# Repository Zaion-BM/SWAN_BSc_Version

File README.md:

# SWAN BSc Thesis
Smart Watering Automation Network (SWAN) is a university thesis project at BME-VIK-MIT

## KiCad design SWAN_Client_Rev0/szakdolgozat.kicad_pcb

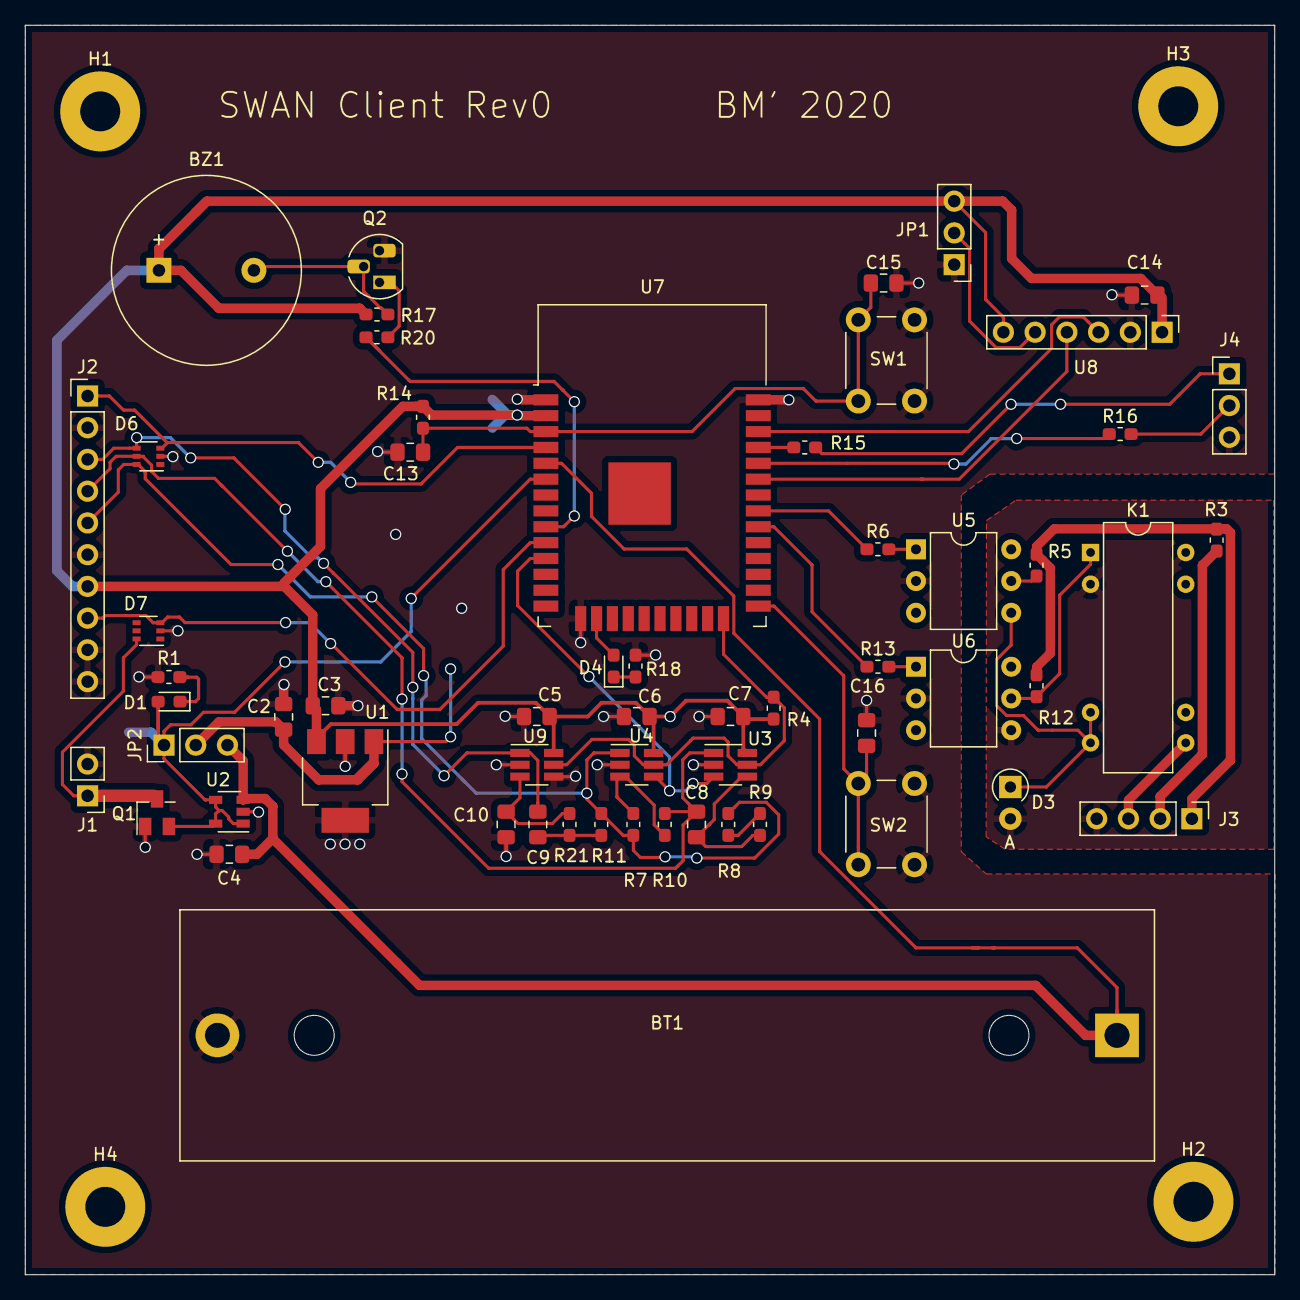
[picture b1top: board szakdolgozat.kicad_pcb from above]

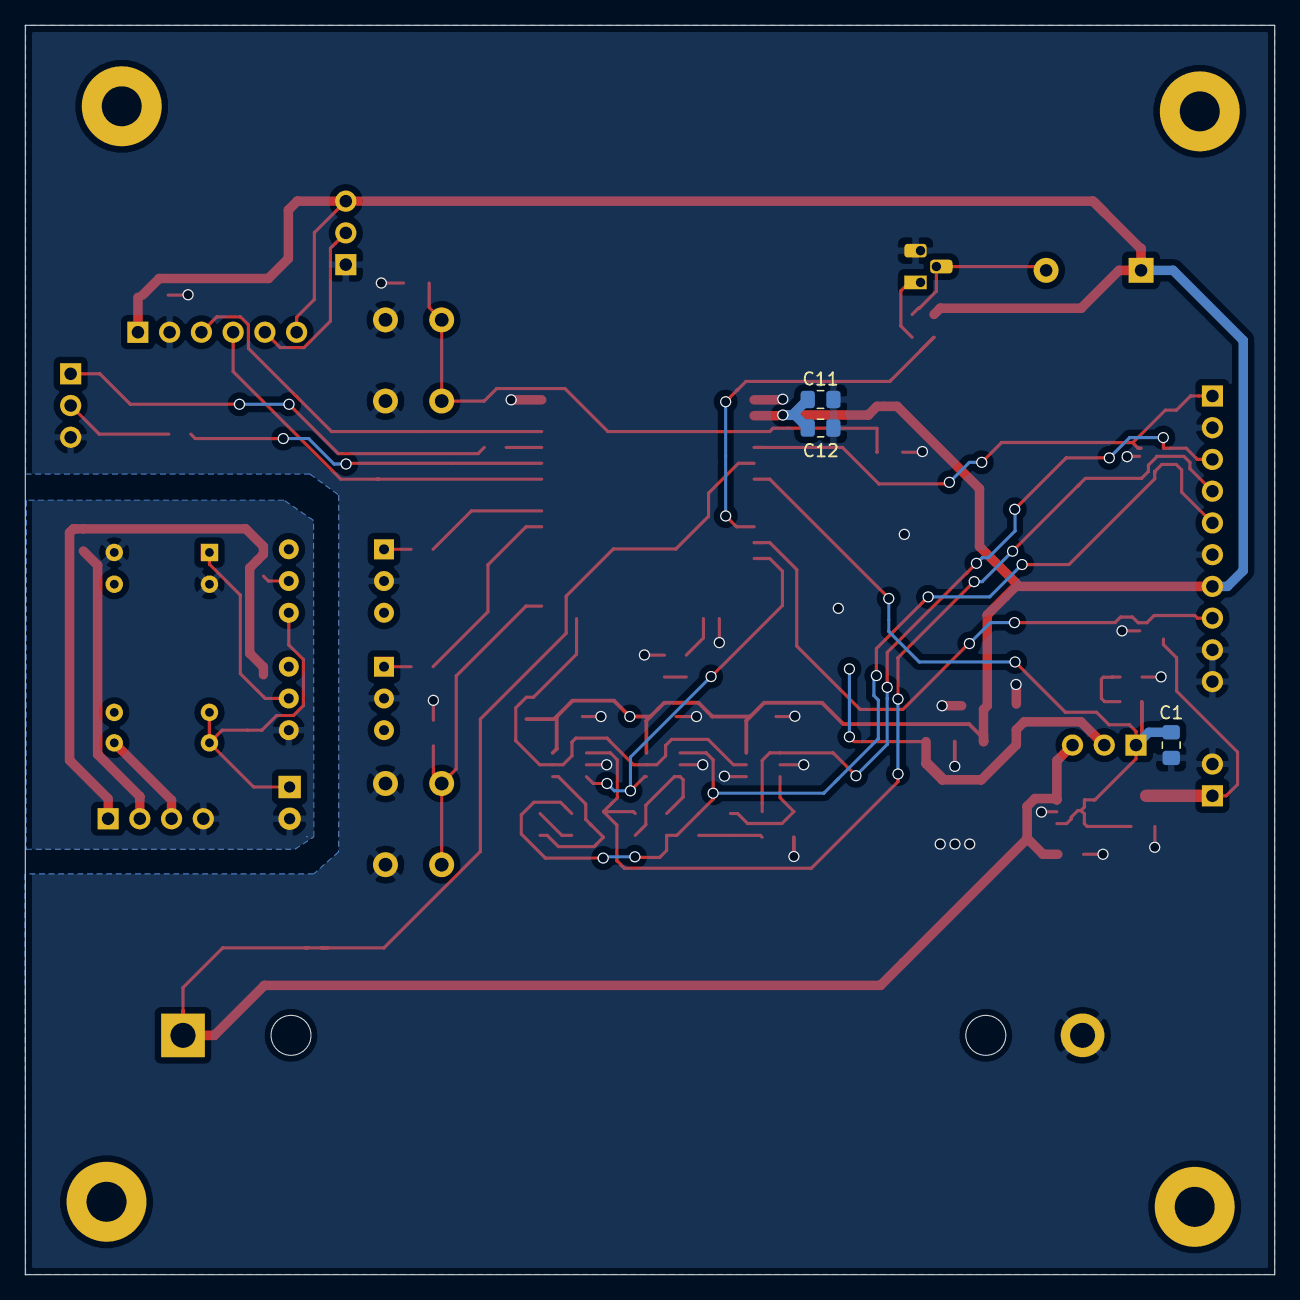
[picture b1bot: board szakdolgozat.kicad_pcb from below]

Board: 2 copper layers, 100.0 x 100.0 mm, 66 parts (3 on the bottom side), 44 nets.

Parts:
BT1: Battery_Cell; BatteryHolder_MPD_BH-18650-PC2
BZ1: Buzzer; Buzzer_15x7.5RM7.6
C1, C2, C3, C4: 1u; C_0805_2012Metric_Pad1.15x1.40mm_HandSolder
C5, C6, C7, C14: 100n; C_0805_2012Metric_Pad1.15x1.40mm_HandSolder
C8: 100p; C_0805_2012Metric_Pad1.15x1.40mm_HandSolder
C9, C10: 10p; C_0805_2012Metric_Pad1.15x1.40mm_HandSolder
C11, C13, C15, C16: 0.1u; C_0805_2012Metric_Pad1.15x1.40mm_HandSolder
C12: 22u; C_0805_2012Metric_Pad1.15x1.40mm_HandSolder
D1, D4: LED; LED_0603_1608Metric_Pad1.05x0.95mm_HandSolder
D3: D; D_A-405_P2.54mm_Vertical_AnodeUp
D6, D7: SP0505BAJT; SOT-363_SC-70-6
H1, H2, H3, H4: MountingHole; MountingHole_3.2mm_M3_Pad
J1: Barrel_Jack; PinHeader_1x02_P2.54mm_Vertical
J2: Conn_01x10_Female; PinHeader_1x10_P2.54mm_Vertical
J3: Conn_01x04_Female; PinHeader_1x04_P2.54mm_Vertical
J4: Conn_01x03_Female; PinHeader_1x03_P2.54mm_Vertical
JP1, JP2: Jumper_NC_Dual; PinHeader_1x03_P2.54mm_Vertical
K1: DIPxx-2Axx-21x; Relay_StandexMeder_DIP_LowProfile
Q1: Q_PMOS_DGS; MySuperSOT-3
Q2: Q_NPN_BCE; TO-92_HandSolder
R1, R14, R17, R18, R20: R; R_0603_1608Metric_Pad1.05x0.95mm_HandSolder
R3: 24R; R_0603_1608Metric_Pad1.05x0.95mm_HandSolder
R4: 100k; R_0603_1608Metric_Pad1.05x0.95mm_HandSolder
R5, R12: 12k; R_0603_1608Metric_Pad1.05x0.95mm_HandSolder
R6, R13: 160R; R_0603_1608Metric_Pad1.05x0.95mm_HandSolder
R7: 68k; R_0603_1608Metric_Pad1.05x0.95mm_HandSolder
R8: 1k; R_0603_1608Metric_Pad1.05x0.95mm_HandSolder
R9: 47; R_0603_1608Metric_Pad1.05x0.95mm_HandSolder
R10, R11, R21: 10k; R_0603_1608Metric_Pad1.05x0.95mm_HandSolder
R15, R16: 22R; R_0603_1608Metric_Pad1.05x0.95mm_HandSolder
SW1, SW2: SW_Push; SW_PUSH_6mm
U1: MCP1826S; SOT-223-3_TabPin2
U2: MCP73811T-420I-OT; SOT-23-5
U3, U4, U9: MCP6273-E_CH; SOT-23-6_Handsoldering
U5, U6: CNY17-1; DIP-6_W7.62mm
U7: ESP32-WROOM-32
U8: BMP280_PCB; PinHeader_1x06_P2.54mm_Vertical

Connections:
+3V3: BZ1.1, C3.1, C5.1, C6.1, C7.1, C11.1, C12.1, C14.1, J2.7, JP1.3, R4.1, R14.1, R17.1, U1.3, U3.6, U4.6, U7.2, U8.1, U8.6, U9.6
+12V: J3.1, R3.1, R5.1, R12.1
/1V65_REF: U3.3, U4.4, U7.11
/#CS: R4.2, U3.5, U4.5, U7.24, U9.5
/Barrel+: D7.6, J1.1, Q1.1
/BatteryIndicator: D4.2, U7.16
/Buzzer: R20.2, U7.9
/DAC1: D7.3, J2.8, U7.10
/EN: C13.1, C15.1, R14.2, SW1.2, U7.3
/IO0: C16.1, SW2.2, U7.25
/RX: J4.2, R16.2
/SCL: U7.36, U8.3
/SDA: U7.33, U8.4
/TX: J4.1, R15.1
/U_moisture: D6.3, J2.1, U7.4
/U_reset: R13.1, U7.30
/U_set: R6.1, U7.31
/Ubat: BT1.1, C4.2, JP2.3, U2.3, U7.5
/Usin: C9.2, D6.4, J2.3, U9.1
/Usquare: D6.6, J2.5, R7.2, R8.1, R11.1, U4.1
/Utriangle: C8.2, D6.5, J2.4, R10.1, U3.1
/Vin: C1.2, D1.2, JP2.1, Q1.3, U2.1, U2.4, U2.5, U7.6
GND: BT1.2, C1.1, C2.2, C3.2, C4.1, C5.2, C6.2, C7.2, C10.1, C11.2, C12.2, C13.2, C14.2, C15.2, C16.2, D6.2, D7.2, J1.2, J2.2, J2.6, J2.9, J2.10, J4.3, JP1.1, Q1.2, Q2.3, R1.2, R18.2, SW1.1, SW2.1, U1.2, U2.2, U3.2, U4.2, U5.2, U6.2, U7.1, U7.15, U7.38, U8.2, U9.2, U9.4
GNDPWR: D3.2, J3.4, K1.2, K1.14, U6.4
unnamed: BZ1.2, Q2.2, R17.2
unnamed: C2.1, JP2.2, U1.1
unnamed: C8.1, R9.2, U3.4
unnamed: C9.1, R11.2, R21.1
unnamed: C10.2, R21.2, U9.3
unnamed: D1.1, R1.1
unnamed: D3.1, K1.6, K1.7, U5.4
unnamed: D4.1, R18.1
unnamed: J3.2, R3.2
unnamed: J3.3, K1.8
unnamed: JP1.2, U8.5
unnamed: K1.1, R12.2, U6.5
unnamed: Q2.1, R20.1
unnamed: R5.2, U5.5
unnamed: R6.2, U5.1
unnamed: R8.2, R9.1
unnamed: R7.1, R10.2, U4.3
unnamed: R13.2, U6.1
unnamed: R15.2, U7.35
unnamed: R16.1, U7.34

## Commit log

2020-11-06 Logo added
2020-11-06 Thesis template added
    Contains intro too.
2020-11-06 PCB Rev0 added
    Rev0 went to prototype production
2020-11-06 Price of clientPCB added
2020-11-06 System design files added
    Contains .io .pdf .png
2020-11-06 schematic export added
2020-11-06 PCB layers pdf export added
2020-11-06 Initial client firmware added
    No WIFI, just I2C ADC and sleep
2020-11-06 Intro section done
2020-11-07 Datasheets added
    Contains datasheets of all the IC-s
2020-11-09 Document until LDO finished
2020-11-16 Schematic documentation done
2020-11-16 Reference voltage for AWG is fixed
2020-11-16 MQTT, DAC tasks added
2020-11-18 Deep sleep added, WIFI&MQTT STACKSIZE fixed
2020-11-21 MQTT receive is added
2020-11-22 Finished firmware without serialnumber.
    Serialnumber to be added later.
2020-11-23 Firmware code added to appendix
2020-11-23 2nd order Sallen-Key Low pass filter's bode plot
2020-11-24 JSON and SQL script for logging added
2020-11-27 Sensor measurement 11_27
2020-11-27 Deep sleep timer to be modified, but finished
2020-11-27 Finialized firmware ver 1.0
    Comments to be added
2020-11-29 Függelék up to date
2020-11-29 Firmware version 1.0
2020-11-29 Server flow version 1.0
2020-12-01 SWAN nodes added
2020-12-01 Node-RED node scripts added
2020-12-01 Server documentation almost finished
2020-12-03 Went to production
2020-12-05 Capacitive measurement documentation added
2020-12-06 2nd chapter finished
2020-12-06 Grammar review required (page 11-18)
2020-12-06 Chapter 1., 2., 3.1, 4.2, 5.2 finished
2020-12-07 All done excluding firmware documentation
2020-12-07 Firmware 1.1
2020-12-07 Finalised document
    Pre consultant review.
    Current measurement missing.
2020-12-09 Final document
    Pre review
2021-03-04 Presentation added.
